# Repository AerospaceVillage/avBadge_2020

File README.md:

# Aerospace Village Badge 2020

This resository is to document and capture all of the engineering and design work that went into creating the [Aerospace Village](https://aerospacevillage.org) Badge for 2020.

The badge is a multifunctional design that is part SWAG, part antenna, part low level protocol interaction. In keeping with the spirit of aviation everything is as small as possible and tries to use as much of the available resources as possible.

You can even use this airplane shaped badge as an anetenna to locate real airplanes transmitting ADS-B. Additionally, you can also use it to capture data from other freqenices (i.e. ACARS) using the built in SMA to wire terminal blocks. Why stop there? You can also interact with your preferred I2C device ([bus pirate](https://learn.sparkfun.com/tutorials/bus-pirate-v36a-hookup-guide/all#introduction)) and control each of the available lighting packages. Alternatively, you could just wear it and look cool.

## Kit Assembly

Instructions for assembing a kit can be found in the Document folder.
    
  - [Tindie Instructions](https://github.com/daneallen/avBadge_2020/blob/master/Documents/Tindie%20Instructions.pdf)
  - [Instructions sent with kit](https://github.com/daneallen/avBadge_2020/blob/master/Documents/Send%20out%20instructions.pdf)

## Arduino Programming
Using the Arduino IDE Add the correct Boards Manager URL:

    - Under File->Preferences add the following URL http://drazzy.com/package_drazzy.com_index.json
    - Then with the new Boards Maanger options select ATTinyCore

Steps:

    - Programmer - USBTinyISP
    - Clock 8MHZ
    - Burn Bootloader
    - Upload using programmer

## AVR Programming

[device permissions help](https://andreasrohner.at/posts/Electronics/How-to-fix-device-permissions-for-the-USBasp-programmer/)

[ttyACM permission](https://stackoverflow.com/questions/40951728/avrdude-ser-open-cant-open-device-dev-ttyacm0-device-or-resource-busy)

```
sudo adduser <username> dialout
$ sudo chmod a+rw /dev/ttyACM0
```

## Hardware
The ATtiny85 is programmed with the [Sparkfun Tiny AVR Programmer](https://www.sparkfun.com/products/11801) using the [SparkFun ISP Pogo Adapter](https://www.sparkfun.com/products/11591)

## Lanyard Modification
Check out the .stl files in the /sma lanyard folder that you can print to more easily turn the badge into a wearable lanyard.

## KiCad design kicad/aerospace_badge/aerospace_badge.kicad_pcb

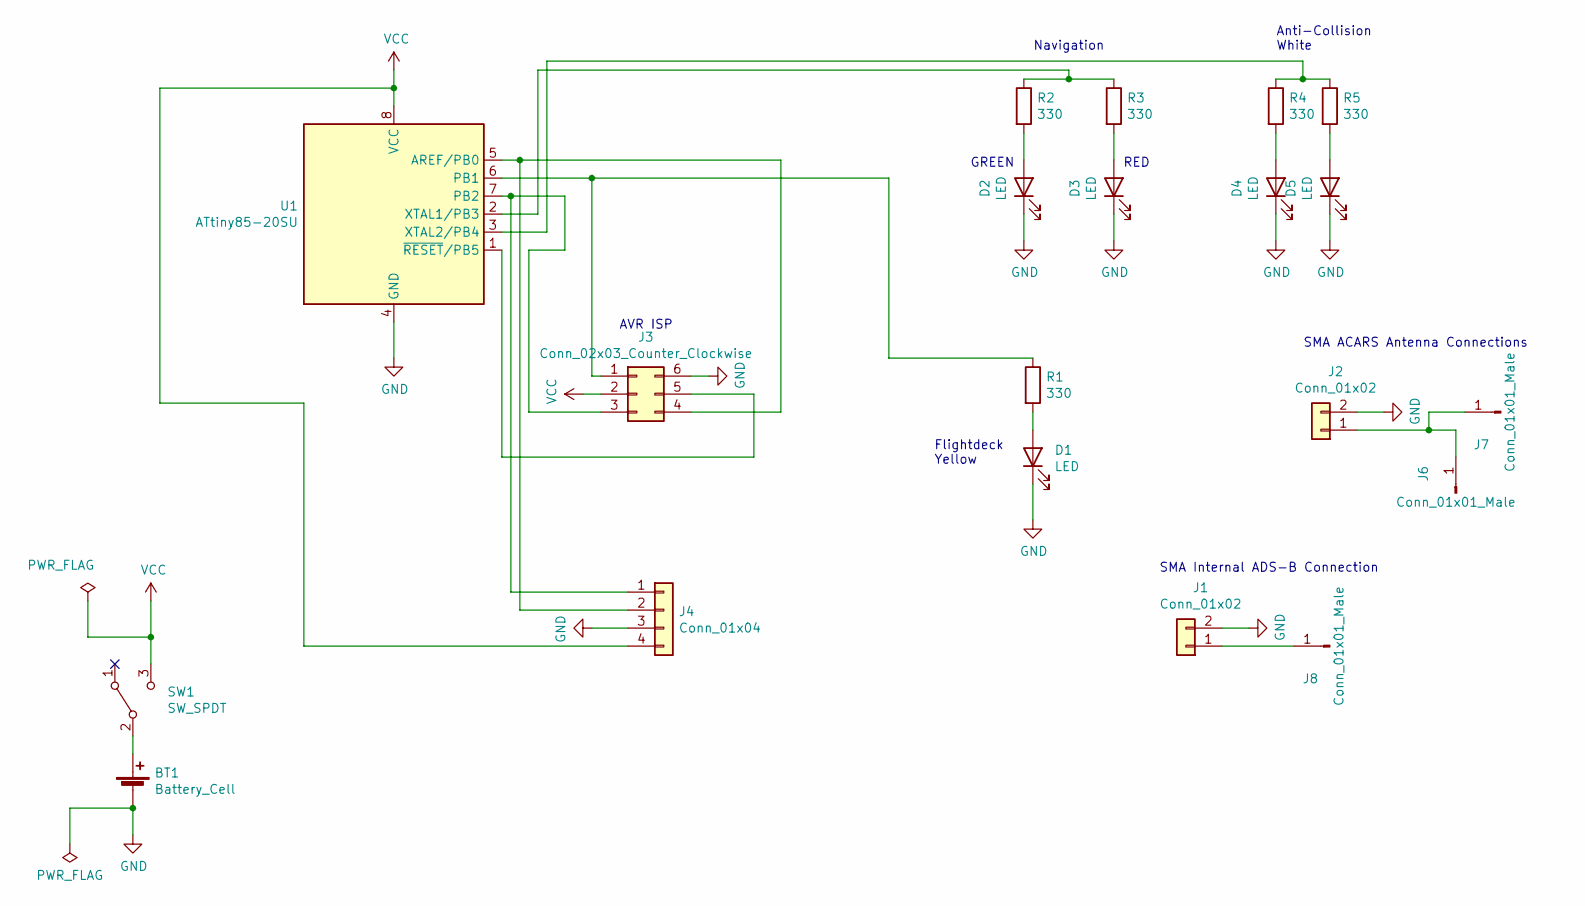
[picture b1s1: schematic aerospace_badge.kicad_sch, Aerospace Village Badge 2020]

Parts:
BT1: Battery_Cell; BatteryHolder_Keystone_3034_1x20mm
D1: LED; XZMYK45WT-9
D2: LED; XZDGK45WT-9
D3: LED; XZM2CRK45WT-9
D4, D5: LED; led_in-s124ar
J1, J2: Conn_01x02; linx_sma_jack_female_socket
J3: Conn_02x03_Counter_Clockwise; isp_pad
J4: Conn_01x04; PinHeader_1x04_P2.54mm_Vertical
J6, J7: Conn_01x01_Male; wire_terminal_sr99s01
J8: Conn_01x01_Male; badge_v02
R1, R2, R3, R4, R5: 330; R_1206_3216Metric
SW1: SW_SPDT; switch_JS202011SCQN
U1: ATtiny85-20SU; SOIJ-8_5.3x5.3mm_P1.27mm

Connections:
GND: BT1.2 (-), D1.1 (K), D2.1 (K), D3.1 (K), D4.1 (K), D5.1 (K), J1.2, J2.2, J3.6, J4.3, U1.4 (GND)
unnamed: BT1.1 (+), SW1.2 (B)
unnamed: D1.2 (A), R1.2
unnamed: D2.2 (A), R2.2
unnamed: D3.2 (A), R3.2
unnamed: D4.2 (A), R4.2
unnamed: D5.2 (A), R5.2
unnamed: J1.1, J8.1
unnamed: J2.1, J6.1, J7.1
unnamed: J3.1, R1.1, U1.6 (PB1)
unnamed: J3.3, J4.1, U1.7 (PB2)
unnamed: J3.4, J4.2, U1.5 (AREF/PB0)
unnamed: J3.5, U1.1 (~RESET/PB5)
unnamed: R2.1, R3.1, U1.2 (XTAL1/PB3)
unnamed: R4.1, R5.1, U1.3 (XTAL2/PB4)
VCC: J3.2, J4.4, SW1.3 (C), U1.8 (VCC)

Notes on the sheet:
SMA Internal ADS-B Connection
Anti-Collision White
AVR ISP
Navigation
SMA ACARS Antenna Connections
Flightdeck Yellow
RED
GREEN

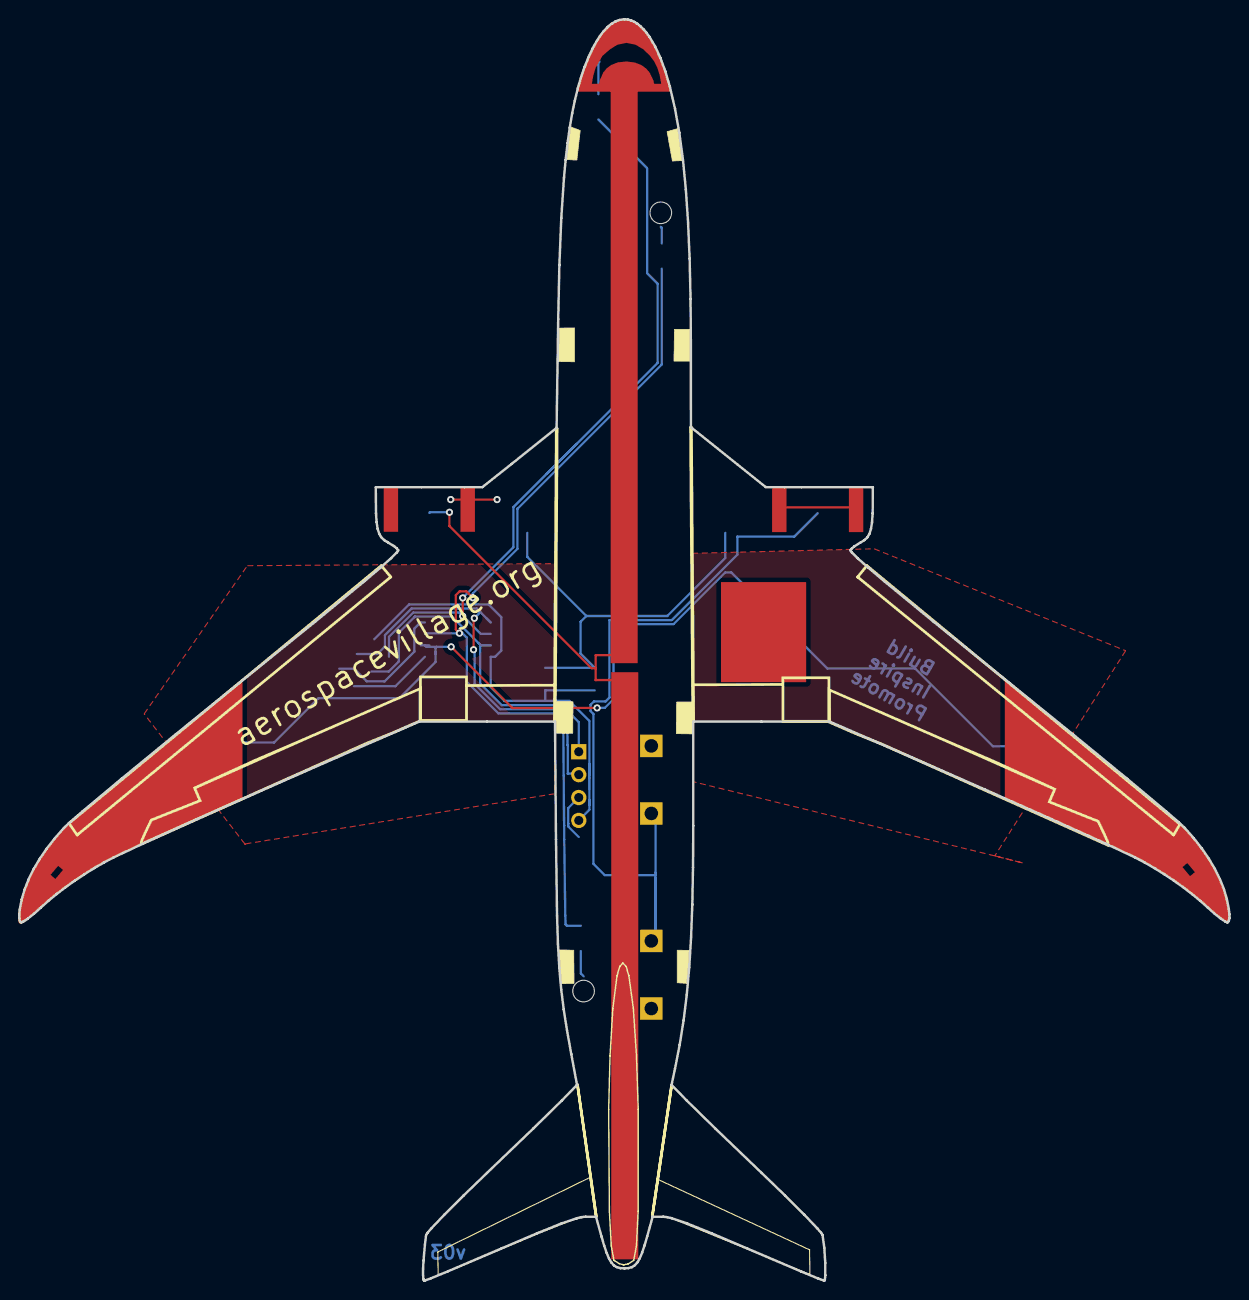
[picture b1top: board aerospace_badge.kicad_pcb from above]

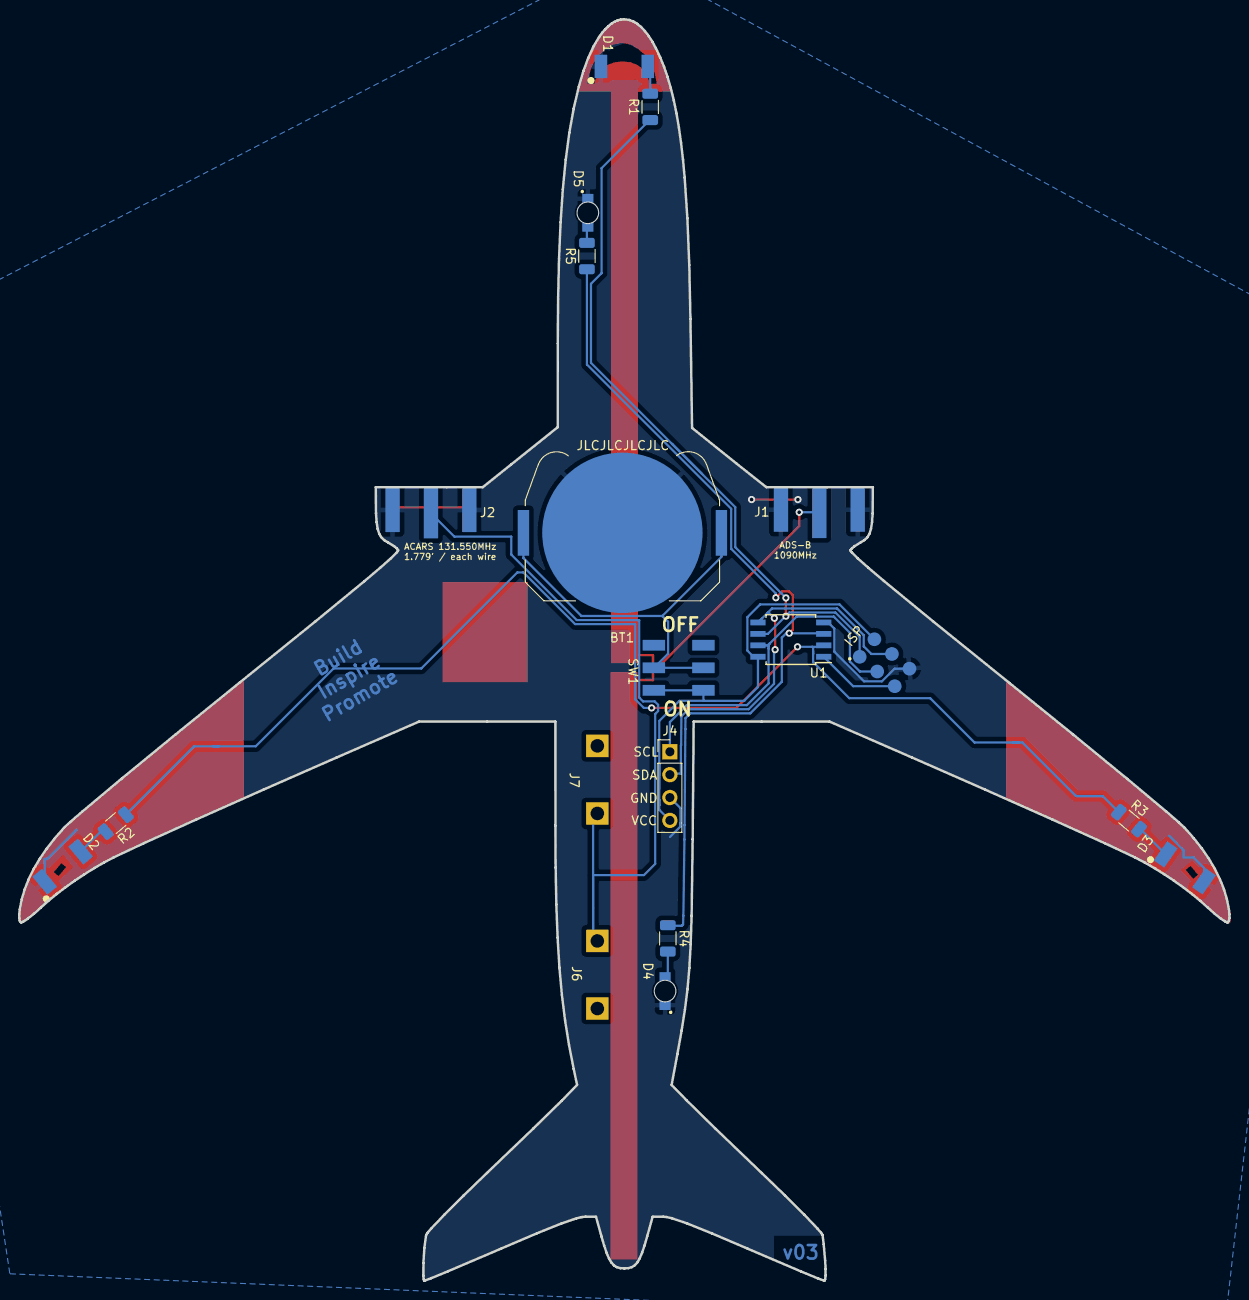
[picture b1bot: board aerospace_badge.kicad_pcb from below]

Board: 2 copper layers, 134.3 x 140.0 mm, 20 parts (17 on the bottom side), 16 nets.

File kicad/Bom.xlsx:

PCB | Manufacturer Part Number | Manufacturer | Digi-Key Part Number | Customer Reference | Reference Designator | Packaging | Part Status | Quantity | Unit Price | Extended Price | Quantity Available | Mfg Std Lead Time | Description | RoHS Status | Lead Free Status | REACH Status
J2, J4 | CONSMA020.062-G | Linx Technologies Inc. | 343-CONSMA020.062-G-ND |  |  | Tray | Active | 2 | 2.96 | 5.92 | 3254 | 12 Weeks | CONN SMA FML EDGE MNT 0.062" PCB | ROHS3 Compliant | Lead free | Not Available
D3 | XZM2CRK45WT-9 | SunLED | 1497-1332-1-ND |  |  | Cut Tape (CT) | Active | 1 | 0.66 | 0.66 | 139 | 12 Weeks | LED RED CLEAR 2PLCC SMD | ROHS3 Compliant | Lead free | REACH Unaffected
D2 | XZDGK45WT-9 | SunLED | 1497-1337-1-ND |  |  | Cut Tape (CT) | Active | 1 | 0.74 | 0.74 | 110814 | 12 Weeks | LED GREEN CLEAR 2PLCC | ROHS3 Compliant | Lead free | Not Available
D1, D4, D5 | XZMYK45WT-9 | SunLED | 1497-1334-1-ND |  |  | Cut Tape (CT) | Active | 3 | 0.54 | 1.62 | 11358 | 12 Weeks | LED YELLOW CLEAR 2PLCC SMD | ROHS3 Compliant | Lead free | REACH Unaffected
R1-R5 | RC1206FR-07330RL | Yageo | 311-330FRCT-ND |  |  | Cut Tape (CT) | Active | 5 | 0.1 | 0.5 | 52805 | 24 Weeks | RES SMD 330 OHM 1% 1/4W 1206 | ROHS3 Compliant | Lead free | REACH Unaffected
U1 | ATTINY85-20SUR | Microchip Technology | ATTINY85-20SURCT-ND |  |  | Cut Tape (CT) | Active | 1 | 1.19 | 1.19 | 9888 | 15 Weeks | IC MCU 8BIT 8KB FLASH 8SOIC | ROHS3 Compliant | Lead free | REACH Unaffected
BT1 | 3034 | Keystone Electronics | 36-3034-ND |  |  | Bulk | Active | 1 | 0.31 | 0.31 | 38004 | 6 Weeks | BATTERY RETAINER COIN 20MM SMD | ROHS3 Compliant | Lead free | REACH Unaffected
 |  |  |  |  |  |  |  |  |  | 10.94

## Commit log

2020-06-17 Initial repo creation
    Organized and created the repo so that others can collaborate
2020-06-17 updated footprints per new datasheets.
2020-06-19 updated image for larger antenna and flightdeck front copper.
2020-06-19 svg2mod changes of svg to footprint.
2020-06-19 updated BOM for v02
2020-06-19 updated bom from csv to xls
2020-06-22 updated, needs another check prior to fabrication.
2020-06-22 open windows weren't saved... they are now.
2020-06-22 new datasheet and closing checks.
2020-06-22 subtle distance added between wire terminal connectors.
2020-06-22 nearly complete, small checks/tweaks ongoing.
2020-06-22 final review with new gerbers and zip.
2020-06-22 not even sure what the difference is/was.
2020-06-22 f.silk fueslage line not as thick on right vs. left. Fixed.
2020-06-22 fixed svg file to make lines match.
2020-06-23 jlcpcb rejected because traces too close to edge, trace refactor.
2020-06-23 including new gerber zip bundle.
2020-07-08 updated BOM from digikey
2020-07-08 organizing and finalizing.
2020-07-09 Update README.md
    Spelling correction
2020-07-09 preserve original gerber zip but move away from main folder for posterity.
2020-07-18 including helpful assembly documents.
2020-07-18 changed message over IC2.
2020-07-30 adding assembly isntructions.
2020-07-30 fixed pdf that was absurdly large.
2020-07-31 SMA caps to add jumper ring for lanyard
    Print at .2mm or finer. It's a tight initial turn, but once on, easy to screw on and off. Use a jumper ring and clip lanyard with lobster clasp of your choice.
2023-06-05 cosmetic updates and KiCad version update, footprint inclusions
